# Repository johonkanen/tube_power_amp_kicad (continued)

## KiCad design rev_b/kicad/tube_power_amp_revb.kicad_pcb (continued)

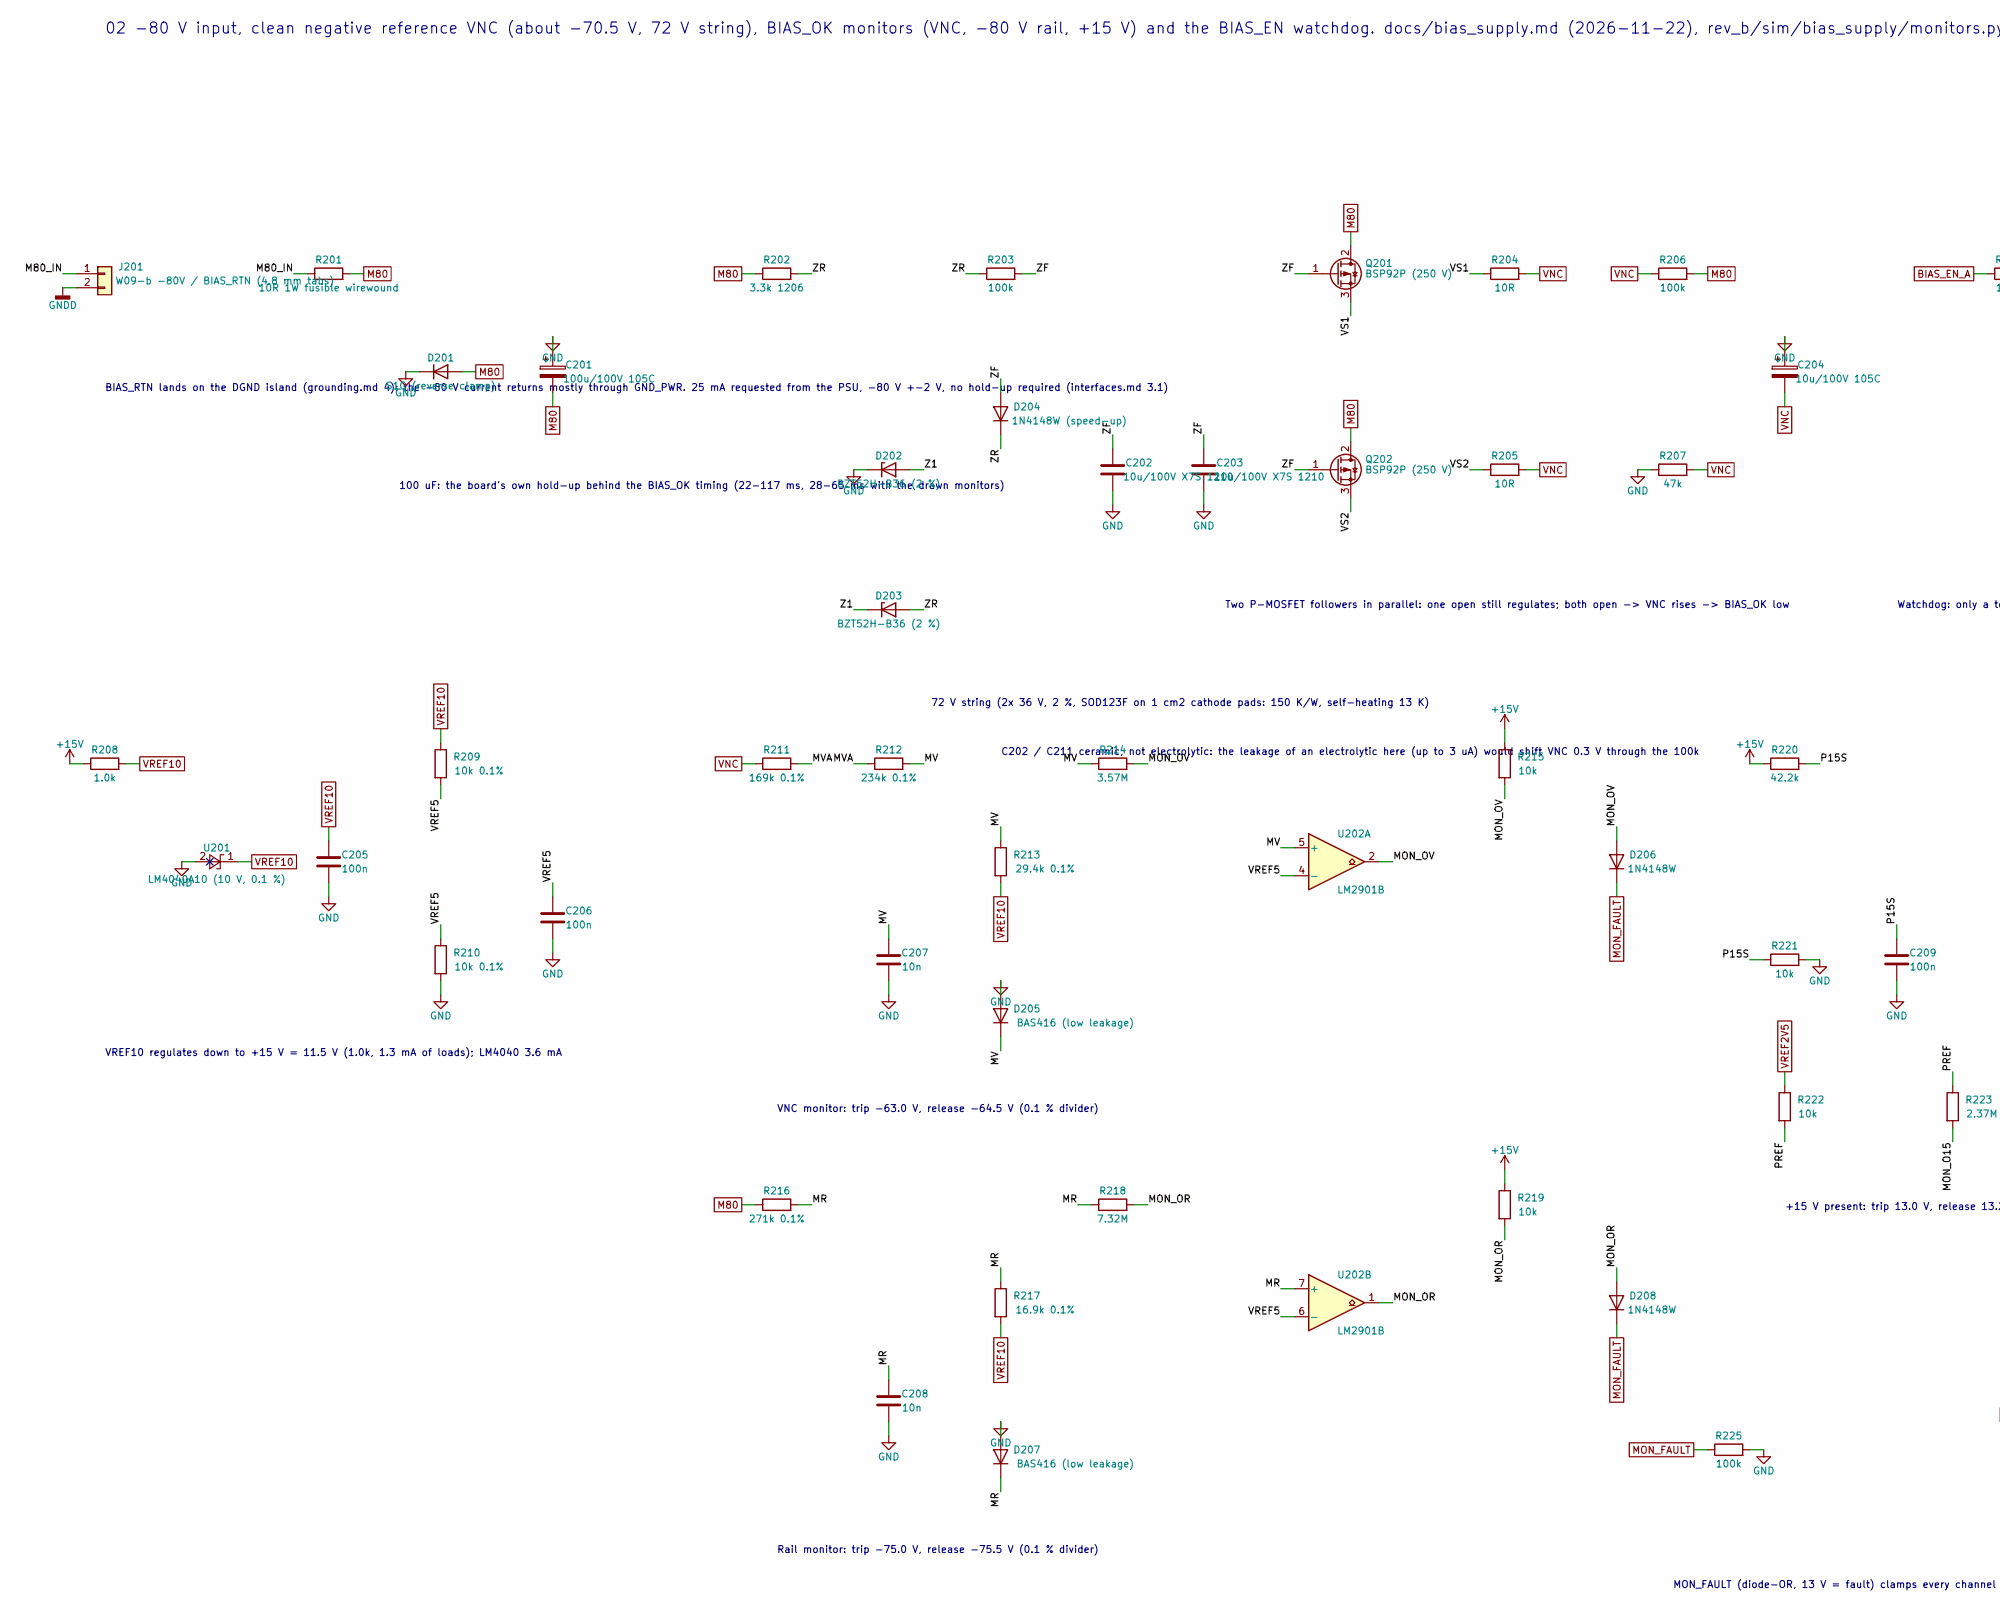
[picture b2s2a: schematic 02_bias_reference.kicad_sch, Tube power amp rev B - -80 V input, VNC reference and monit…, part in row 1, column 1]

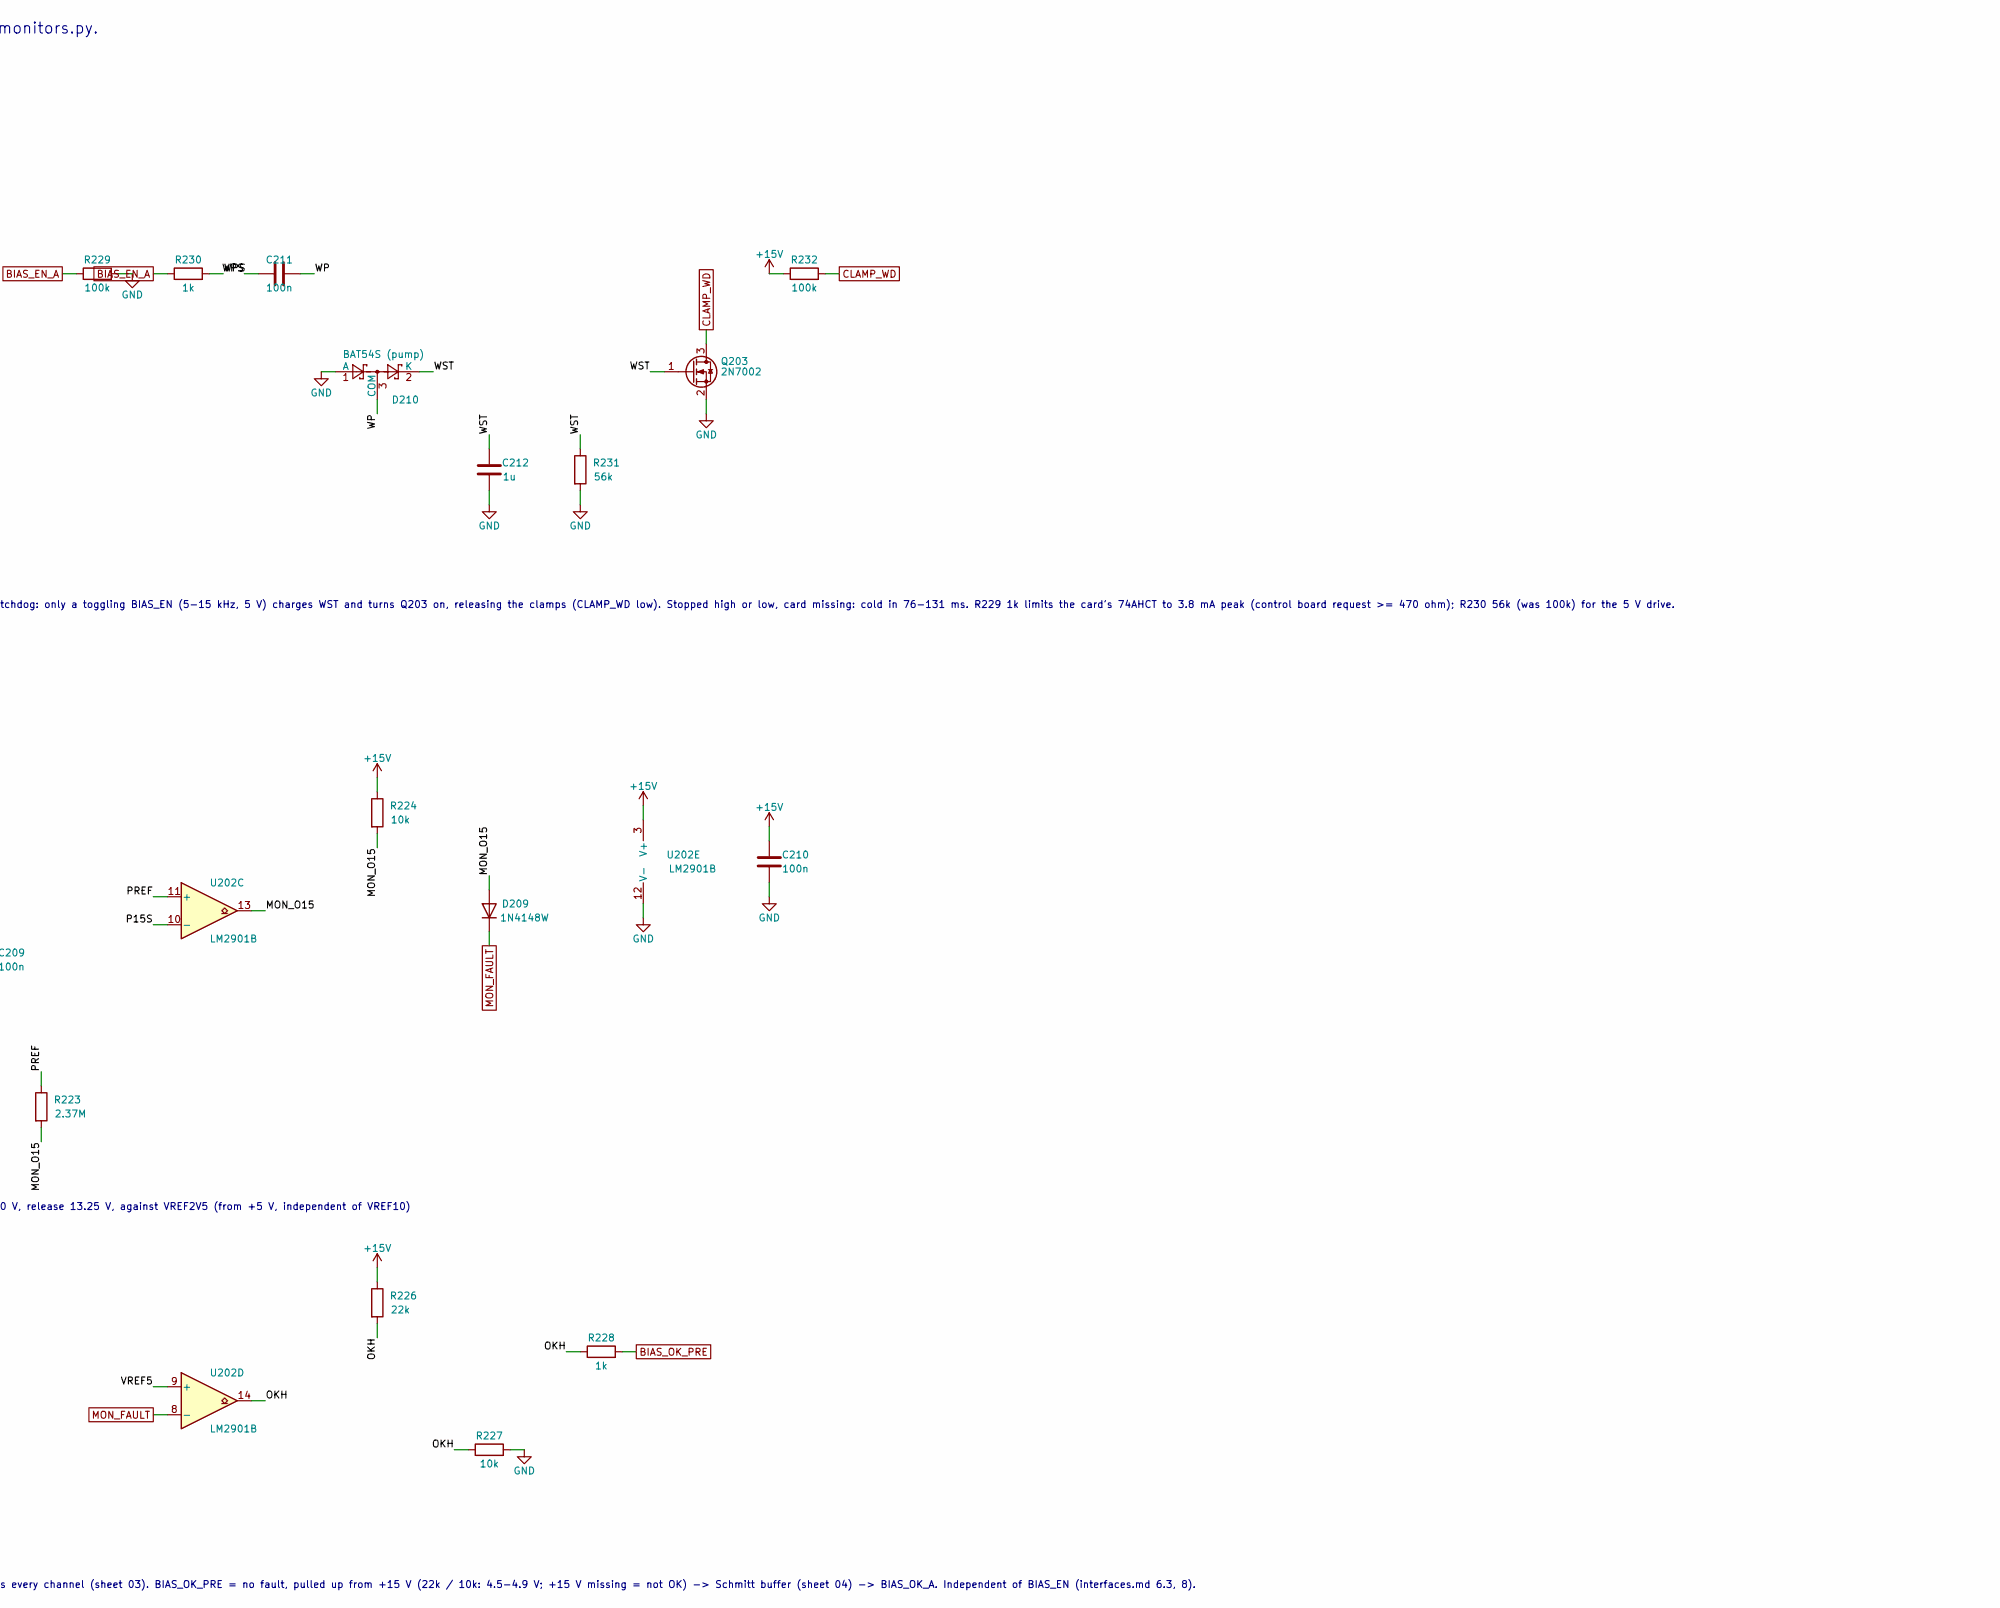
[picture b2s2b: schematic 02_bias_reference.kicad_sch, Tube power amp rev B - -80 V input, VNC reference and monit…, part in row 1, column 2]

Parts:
C201: 100u/100V 105C; CP_Radial_D10.0mm_P5.00mm
C202, C203: 10u/100V X7S 1210; C_1210_3225Metric
C204: 10u/100V 105C; CP_Radial_D6.3mm_P2.50mm
C205, C206, C209, C210, C211: 100n; C_0603_1608Metric
C207, C208: 10n; C_0603_1608Metric
C212: 1u; C_0603_1608Metric
D201: S1G (reverse clamp); D_SMA
D202, D203: BZT52H-B36 (2 %); D_SOD-123F
D204: 1N4148W (speed-up); D_SOD-123
D205, D207: BAS416 (low leakage); D_SOD-323
D206, D208, D209: 1N4148W; D_SOD-123
D210: BAT54S (pump); SOT-23
J201: W09-b -80V / BIAS_RTN (4.8 mm tabs); BladeTab_4.8mm_x2_P9.50mm
Q201, Q202: BSP92P (250 V); SOT-223-3_TabPin2
Q203: 2N7002; SOT-23
R201: 10R 1W fusible wirewound; R_Axial_DIN0309_L9.0mm_D3.2mm_P12.70mm_Horizontal
R202: 3.3k 1206; R_1206_3216Metric
R203, R206, R225, R229, R232: 100k; R_0603_1608Metric
R204, R205: 10R; R_0603_1608Metric
R207: 47k; R_0603_1608Metric
R208: 1.0k; R_1206_3216Metric
R209, R210: 10k 0.1%; R_1206_3216Metric
R211: 169k 0.1%; R_1206_3216Metric
R212: 234k 0.1%; R_1206_3216Metric
R213: 29.4k 0.1%; R_1206_3216Metric
R214: 3.57M; R_1206_3216Metric
R215, R219, R221, R222, R224, R227: 10k; R_0603_1608Metric
R216: 271k 0.1%; R_1206_3216Metric
R217: 16.9k 0.1%; R_1206_3216Metric
R218: 7.32M; R_1206_3216Metric
R220: 42.2k; R_0603_1608Metric
R223: 2.37M; R_1206_3216Metric
R226: 22k; R_0603_1608Metric
R228, R230: 1k; R_0603_1608Metric
R231: 56k; R_0603_1608Metric
U201: LM4040A10 (10 V, 0.1 %); SOT-23
U202: LM2901B; SOIC-14_3.9x8.7mm_P1.27mm

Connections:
+15V: C210.1, R208.1, R215.1, R219.1, R220.1, R224.1, R226.1, R232.1, U202.3 (V+); also elsewhere on the board
/02 -80 V input, VNC reference and monitor, watchdog/M80_IN: J201.1, R201.1
/02 -80 V input, VNC reference and monitor, watchdog/MON_O15: D209.2 (A), R223.2, R224.2, U202.13
/02 -80 V input, VNC reference and monitor, watchdog/MON_OR: D208.2 (A), R218.2, R219.2, U202.1
/02 -80 V input, VNC reference and monitor, watchdog/MON_OV: D206.2 (A), R214.2, R215.2, U202.2
/02 -80 V input, VNC reference and monitor, watchdog/MR: C208.1, D207.1 (K), R216.2, R217.1, R218.1, U202.7 (+)
/02 -80 V input, VNC reference and monitor, watchdog/MV: C207.1, D205.1 (K), R212.2, R213.1, R214.1, U202.5 (+)
/02 -80 V input, VNC reference and monitor, watchdog/MVA: R211.2, R212.1
/02 -80 V input, VNC reference and monitor, watchdog/OKH: R226.2, R227.1, R228.1, U202.14
/02 -80 V input, VNC reference and monitor, watchdog/P15S: C209.1, R220.2, R221.1, U202.10 (-)
/02 -80 V input, VNC reference and monitor, watchdog/PREF: R222.2, R223.1, U202.11 (+)
/02 -80 V input, VNC reference and monitor, watchdog/VREF5: C206.1, R209.2, R210.1, U202.4 (-), U202.6 (-), U202.9 (+)
/02 -80 V input, VNC reference and monitor, watchdog/VS1: Q201.3 (S), R204.1
/02 -80 V input, VNC reference and monitor, watchdog/VS2: Q202.3 (S), R205.1
/02 -80 V input, VNC reference and monitor, watchdog/WP: C211.2, D210.3 (COM)
/02 -80 V input, VNC reference and monitor, watchdog/WPS: C211.1, R230.2
/02 -80 V input, VNC reference and monitor, watchdog/WST: C212.1, D210.2 (K), Q203.1 (G), R231.1
/02 -80 V input, VNC reference and monitor, watchdog/Z1: D202.2 (A), D203.1 (K)
/02 -80 V input, VNC reference and monitor, watchdog/ZF: C202.1, C203.1, D204.2 (A), Q201.1 (G), Q202.1 (G), R203.2
/02 -80 V input, VNC reference and monitor, watchdog/ZR: D203.2 (A), D204.1 (K), R202.2, R203.1
BIAS_EN_A: R229.1, R230.1; also elsewhere on the board
BIAS_OK_PRE: R228.2; also elsewhere on the board
CLAMP_WD: Q203.3 (D), R232.2; also elsewhere on the board
GND: C201.1, C202.2, C203.2, C204.1, C205.2, C206.2, C207.2, C208.2, C209.2, C210.2, C212.2, D201.1 (K), D202.1 (K), D205.2 (A), D207.2 (A), D210.1 (A), Q203.2 (S), R207.1, R210.2, R221.2, R225.2, R227.2, R229.2, R231.2, U201.2 (A), U202.12 (V-); also elsewhere on the board
GNDD: J201.2; also elsewhere on the board
M80: C201.2, D201.2 (A), Q201.2 (D), Q202.2 (D), R201.2, R202.1, R206.2, R216.1; also elsewhere on the board
MON_FAULT: D206.1 (K), D208.1 (K), D209.1 (K), R225.1, U202.8 (-); also elsewhere on the board
VNC: C204.2, R204.2, R205.2, R206.1, R207.2, R211.1; also elsewhere on the board
VREF2V5: R222.1; also elsewhere on the board
VREF10: C205.1, R208.2, R209.1, R213.2, R217.2, U201.1 (K); also elsewhere on the board

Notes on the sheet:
02 -80 V input, clean negative reference VNC (about -70.5 V, 72 V string), BIAS_OK monitors (VNC, -80 V rail, +15 V) and the BIAS_EN watchdog. docs/bias_supply.md (2026-11-22), rev_b/sim/bias_supply/monitors.py.
BIAS_RTN lands on the DGND island (grounding.md 4); the -80 V current returns mostly through GND_PWR. 25 mA requested from the PSU, -80 V +-2 V, no hold-up required (interfaces.md 3.1)
100 uF: the board's own hold-up behind the BIAS_OK timing (22-117 ms, 28-65 ms with the drawn monitors)
72 V string (2x 36 V, 2 %, SOD123F on 1 cm2 cathode pads: 150 K/W, self-heating 13 K)
C202 / C211 ceramic, not electrolytic: the leakage of an electrolytic here (up to 3 uA) would shift VNC 0.3 V through the 100k
Two P-MOSFET followers in parallel: one open still regulates; both open -> VNC rises -> BIAS_OK low
VREF10 regulates down to +15 V = 11.5 V (1.0k, 1.3 mA of loads); LM4040 3.6 mA
VNC monitor: trip -63.0 V, release -64.5 V (0.1 % divider)
Rail monitor: trip -75.0 V, release -75.5 V (0.1 % divider)
+15 V present: trip 13.0 V, release 13.25 V, against VREF2V5 (from +5 V, independent of VREF10)
MON_FAULT (diode-OR, 13 V = fault) clamps every channel (sheet 03). BIAS_OK_PRE = no fault, pulled up from +15 V (22k / 10k: 4.5-4.9 V; +15 V missing = not OK) -> Schmitt buffer (sheet 04) -> BIAS_OK_A. Independent of BIAS_EN (interfaces.md 6.3, 8).
Watchdog: only a toggling BIAS_EN (5-15 kHz, 5 V) charges WST and turns Q203 on, releasing the clamps (CLAMP_WD low). Stopped high or low, card missing: cold in 76-131 ms. R229 1k limits the card's 74AHCT to 3.8 mA peak (control board request >= 470 ohm); R230 56k (was 100k) for the 5 V drive.

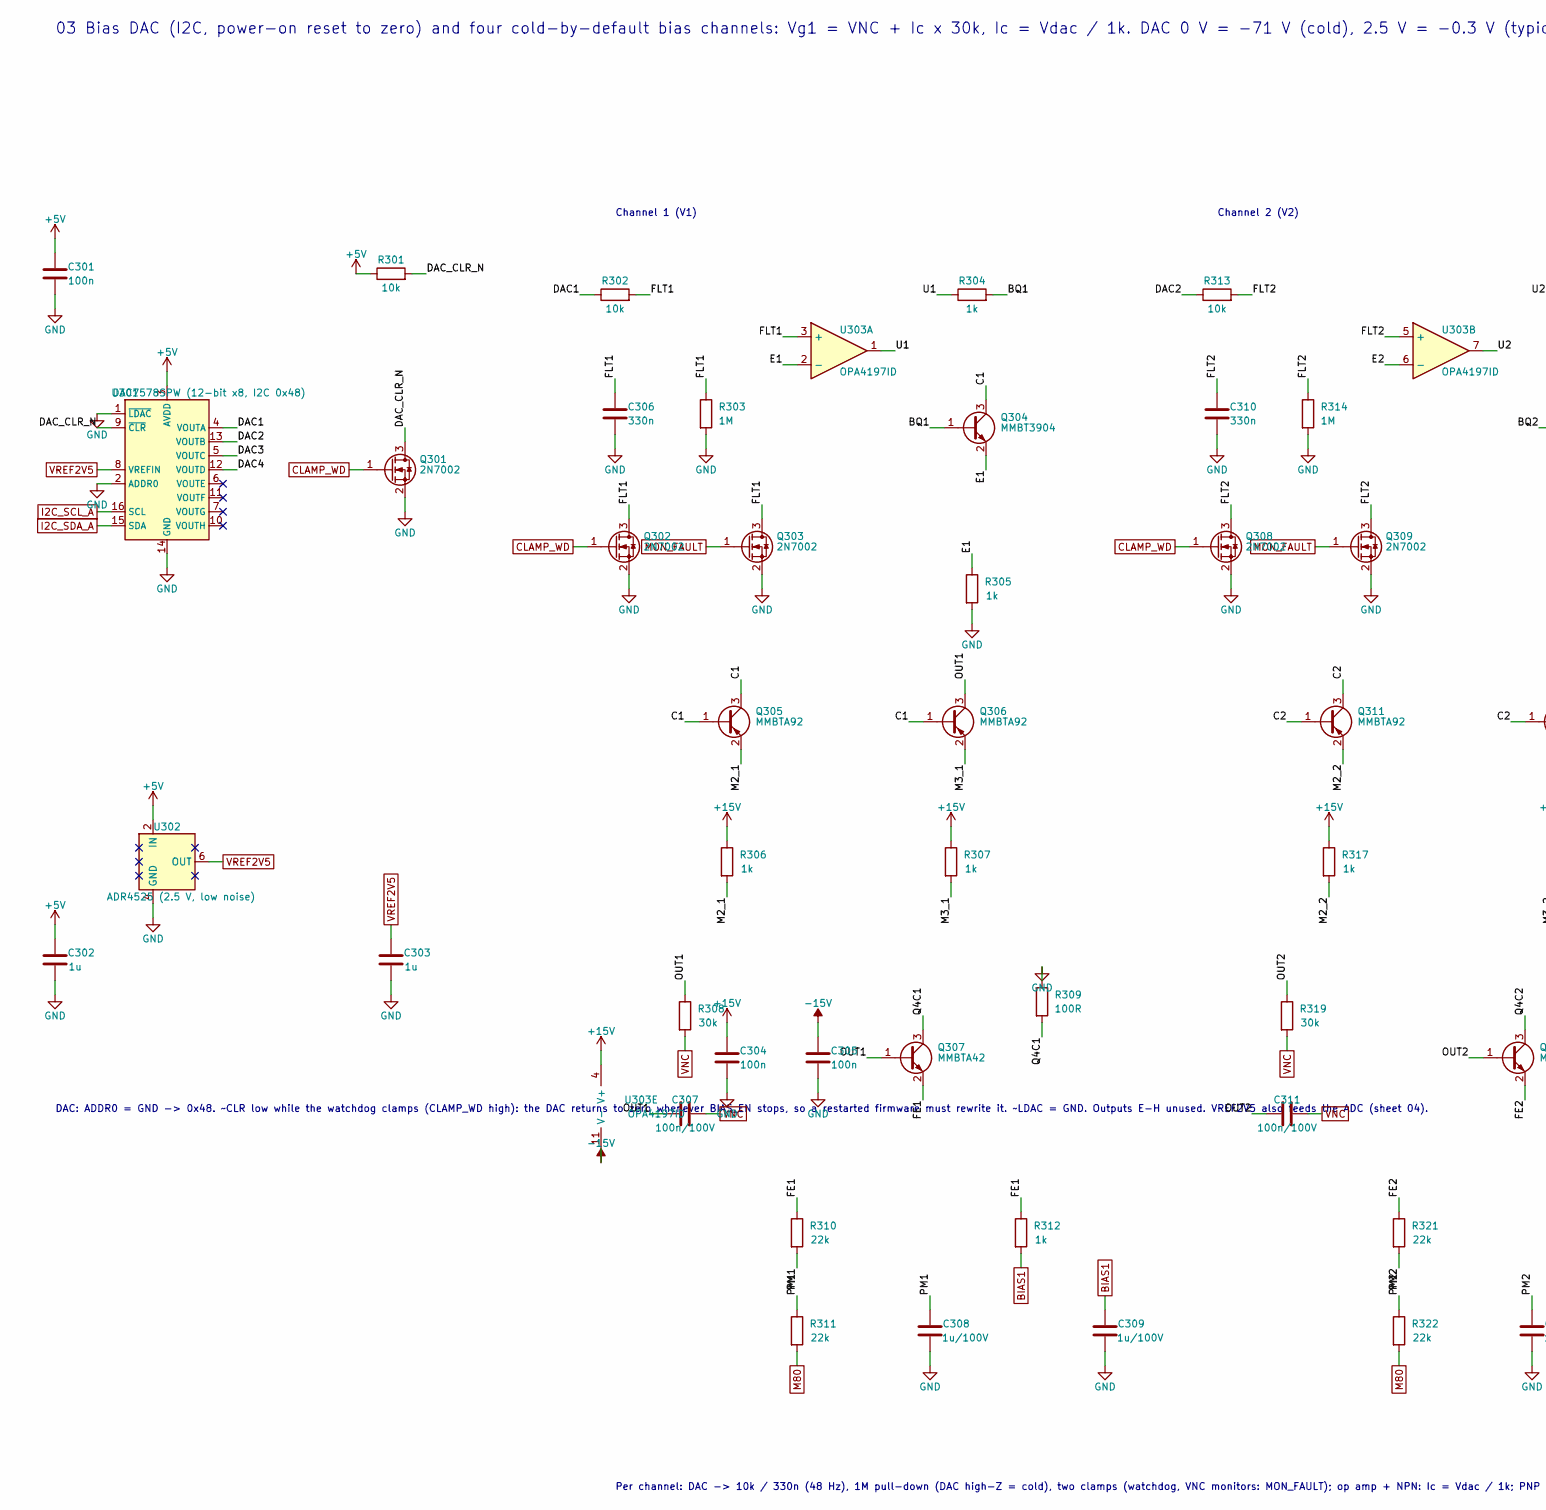
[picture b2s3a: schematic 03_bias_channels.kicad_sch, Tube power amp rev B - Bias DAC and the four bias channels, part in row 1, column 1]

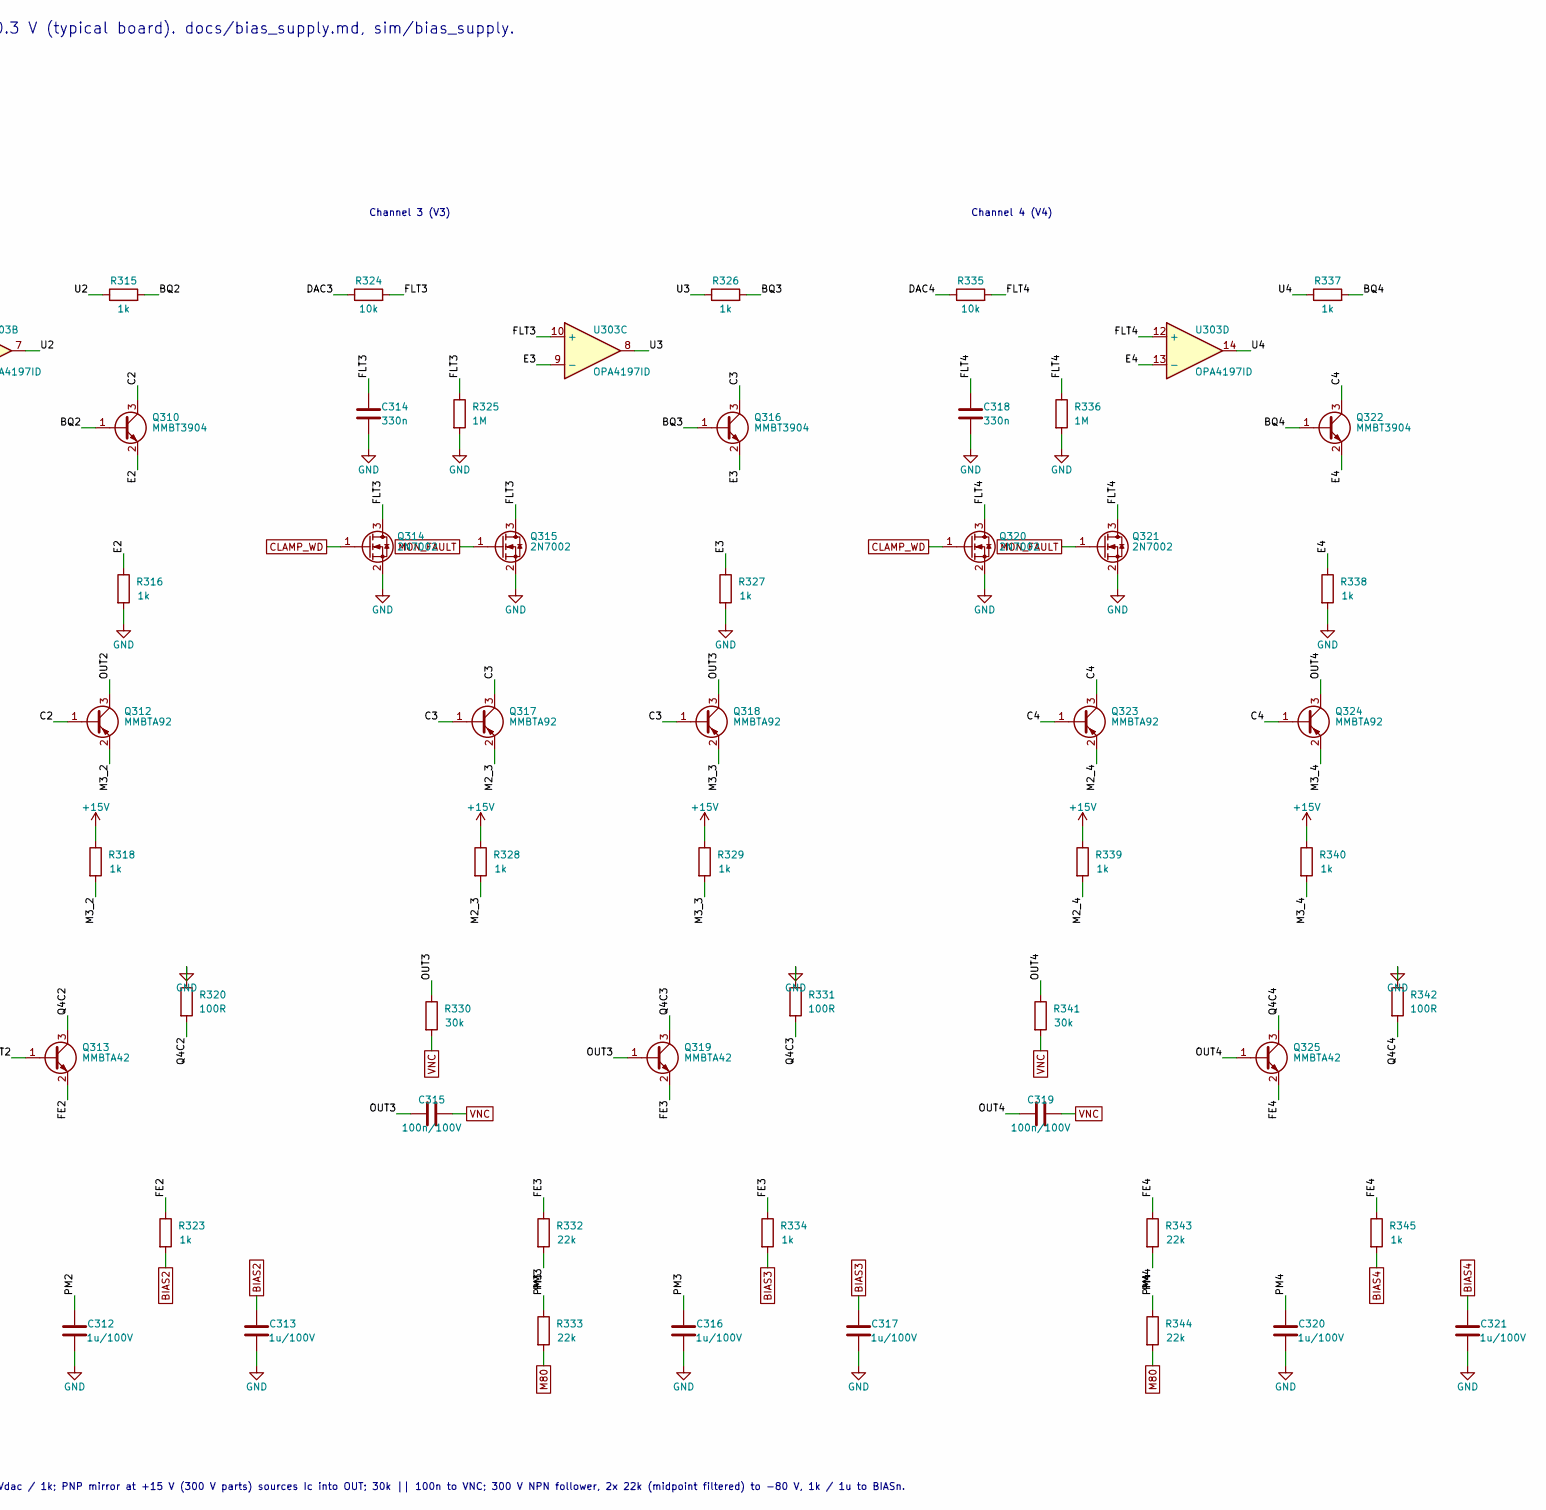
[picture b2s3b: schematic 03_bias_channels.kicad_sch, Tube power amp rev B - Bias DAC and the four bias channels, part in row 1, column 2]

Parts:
C301, C304, C305: 100n; C_0603_1608Metric
C302, C303: 1u; C_0603_1608Metric
C306, C310, C314, C318: 330n; C_0805_2012Metric
C307, C311, C315, C319: 100n/100V; C_0805_2012Metric
C308, C309, C312, C313, C316, C317, C320, C321: 1u/100V; C_0805_2012Metric
Q301, Q302, Q303, Q308, Q309, Q314, Q315, Q320, Q321: 2N7002; SOT-23
Q304, Q310, Q316, Q322: MMBT3904; SOT-23
Q305, Q306, Q311, Q312, Q317, Q318, Q323, Q324: MMBTA92; SOT-23
Q307, Q313, Q319, Q325: MMBTA42; SOT-23
R301, R302, R313, R324, R335: 10k; R_0603_1608Metric
R303, R314, R325, R336: 1M; R_1206_3216Metric
R304, R305, R306, R307, R312, R315, R316, R317, R318, R323, R326, R327, R328, R329, R334, R337, R338, R339, R340, R345: 1k; R_0603_1608Metric
R308, R319, R330, R341: 30k; R_0603_1608Metric
R309, R320, R331, R342: 100R; R_0603_1608Metric
R310, R311, R321, R322, R332, R333, R343, R344: 22k; R_0603_1608Metric
U301: DAC7578SPW (12-bit x8, I2C 0x48); TSSOP-16_4.4x5mm_P0.65mm
U302: ADR4525 (2.5 V, low noise); SOIC-8_3.9x4.9mm_P1.27mm
U303: OPA4197ID; SOIC-14_3.9x8.7mm_P1.27mm

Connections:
+5V: C301.1, C302.1, R301.1, U301.3 (AVDD), U302.2 (IN); also elsewhere on the board
+15V: C304.1, R306.1, R307.1, R317.1, R318.1, R328.1, R329.1, R339.1, R340.1, U303.4 (V+); also elsewhere on the board
-15V: C305.1, U303.11 (V-); also elsewhere on the board
/03 Bias DAC and the four bias channels/BQ1: Q304.1 (B), R304.2
/03 Bias DAC and the four bias channels/BQ2: Q310.1 (B), R315.2
/03 Bias DAC and the four bias channels/BQ3: Q316.1 (B), R326.2
/03 Bias DAC and the four bias channels/BQ4: Q322.1 (B), R337.2
/03 Bias DAC and the four bias channels/C1: Q304.3 (C), Q305.1 (B), Q305.3 (C), Q306.1 (B)
/03 Bias DAC and the four bias channels/C2: Q310.3 (C), Q311.1 (B), Q311.3 (C), Q312.1 (B)
/03 Bias DAC and the four bias channels/C3: Q316.3 (C), Q317.1 (B), Q317.3 (C), Q318.1 (B)
/03 Bias DAC and the four bias channels/C4: Q322.3 (C), Q323.1 (B), Q323.3 (C), Q324.1 (B)
/03 Bias DAC and the four bias channels/DAC1: R302.1, U301.4 (VOUTA)
/03 Bias DAC and the four bias channels/DAC2: R313.1, U301.13 (VOUTB)
/03 Bias DAC and the four bias channels/DAC3: R324.1, U301.5 (VOUTC)
/03 Bias DAC and the four bias channels/DAC4: R335.1, U301.12 (VOUTD)
/03 Bias DAC and the four bias channels/DAC_CLR_N: Q301.3 (D), R301.2, U301.9 (~CLR)
/03 Bias DAC and the four bias channels/E1: Q304.2 (E), R305.1, U303.2 (-)
/03 Bias DAC and the four bias channels/E2: Q310.2 (E), R316.1, U303.6 (-)
/03 Bias DAC and the four bias channels/E3: Q316.2 (E), R327.1, U303.9 (-)
/03 Bias DAC and the four bias channels/E4: Q322.2 (E), R338.1, U303.13 (-)
/03 Bias DAC and the four bias channels/FE1: Q307.2 (E), R310.1, R312.1
/03 Bias DAC and the four bias channels/FE2: Q313.2 (E), R321.1, R323.1
/03 Bias DAC and the four bias channels/FE3: Q319.2 (E), R332.1, R334.1
/03 Bias DAC and the four bias channels/FE4: Q325.2 (E), R343.1, R345.1
/03 Bias DAC and the four bias channels/FLT1: C306.1, Q302.3 (D), Q303.3 (D), R302.2, R303.1, U303.3 (+)
/03 Bias DAC and the four bias channels/FLT2: C310.1, Q308.3 (D), Q309.3 (D), R313.2, R314.1, U303.5 (+)
/03 Bias DAC and the four bias channels/FLT3: C314.1, Q314.3 (D), Q315.3 (D), R324.2, R325.1, U303.10 (+)
/03 Bias DAC and the four bias channels/FLT4: C318.1, Q320.3 (D), Q321.3 (D), R335.2, R336.1, U303.12 (+)
/03 Bias DAC and the four bias channels/M2_1: Q305.2 (E), R306.2
/03 Bias DAC and the four bias channels/M2_2: Q311.2 (E), R317.2
/03 Bias DAC and the four bias channels/M2_3: Q317.2 (E), R328.2
/03 Bias DAC and the four bias channels/M2_4: Q323.2 (E), R339.2
/03 Bias DAC and the four bias channels/M3_1: Q306.2 (E), R307.2
/03 Bias DAC and the four bias channels/M3_2: Q312.2 (E), R318.2
/03 Bias DAC and the four bias channels/M3_3: Q318.2 (E), R329.2
/03 Bias DAC and the four bias channels/M3_4: Q324.2 (E), R340.2
/03 Bias DAC and the four bias channels/OUT1: C307.1, Q306.3 (C), Q307.1 (B), R308.1
/03 Bias DAC and the four bias channels/OUT2: C311.1, Q312.3 (C), Q313.1 (B), R319.1
/03 Bias DAC and the four bias channels/OUT3: C315.1, Q318.3 (C), Q319.1 (B), R330.1
/03 Bias DAC and the four bias channels/OUT4: C319.1, Q324.3 (C), Q325.1 (B), R341.1
/03 Bias DAC and the four bias channels/PM1: C308.1, R310.2, R311.1
/03 Bias DAC and the four bias channels/PM2: C312.1, R321.2, R322.1
/03 Bias DAC and the four bias channels/PM3: C316.1, R332.2, R333.1
/03 Bias DAC and the four bias channels/PM4: C320.1, R343.2, R344.1
/03 Bias DAC and the four bias channels/Q4C1: Q307.3 (C), R309.2
/03 Bias DAC and the four bias channels/Q4C2: Q313.3 (C), R320.2
/03 Bias DAC and the four bias channels/Q4C3: Q319.3 (C), R331.2
/03 Bias DAC and the four bias channels/Q4C4: Q325.3 (C), R342.2
/03 Bias DAC and the four bias channels/U1: R304.1, U303.1
/03 Bias DAC and the four bias channels/U2: R315.1, U303.7
/03 Bias DAC and the four bias channels/U3: R326.1, U303.8
/03 Bias DAC and the four bias channels/U4: R337.1, U303.14
BIAS1: C309.1, R312.2; also elsewhere on the board
BIAS2: C313.1, R323.2; also elsewhere on the board
BIAS3: C317.1, R334.2; also elsewhere on the board
BIAS4: C321.1, R345.2; also elsewhere on the board
CLAMP_WD: Q301.1 (G), Q302.1 (G), Q308.1 (G), Q314.1 (G), Q320.1 (G); also elsewhere on the board
GND: C301.2, C302.2, C303.2, C304.2, C305.2, C306.2, C308.2, C309.2, C310.2, C312.2, C313.2, C314.2, C316.2, C317.2, C318.2, C320.2, C321.2, Q301.2 (S), Q302.2 (S), Q303.2 (S), Q308.2 (S), Q309.2 (S), Q314.2 (S), Q315.2 (S), Q320.2 (S), Q321.2 (S), R303.2, R305.2, R309.1, R314.2, R316.2, R320.1, R325.2, R327.2, R331.1, R336.2, R338.2, R342.1, U301.1 (~LDAC), U301.2 (ADDR0), U301.14 (GND), U302.4 (GND); also elsewhere on the board
I2C_SCL_A: U301.16 (SCL); also elsewhere on the board
I2C_SDA_A: U301.15 (SDA); also elsewhere on the board
M80: R311.2, R322.2, R333.2, R344.2; also elsewhere on the board
MON_FAULT: Q303.1 (G), Q309.1 (G), Q315.1 (G), Q321.1 (G); also elsewhere on the board
VNC: C307.2, C311.2, C315.2, C319.2, R308.2, R319.2, R330.2, R341.2; also elsewhere on the board
VREF2V5: C303.1, U301.8 (VREFIN), U302.6 (OUT); also elsewhere on the board

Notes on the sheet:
03 Bias DAC (I2C, power-on reset to zero) and four cold-by-default bias channels: Vg1 = VNC + Ic x 30k, Ic = Vdac / 1k. DAC 0 V = -71 V (cold), 2.5 V = -0.3 V (typical board). docs/bias_supply.md, sim/bias_supply.
DAC: ADDR0 = GND -> 0x48. ~CLR low while the watchdog clamps (CLAMP_WD high): the DAC returns to zero whenever BIAS_EN stops, so a restarted firmware must rewrite it. ~LDAC = GND. Outputs E-H unused. VREF2V5 also feeds the ADC (sheet 04).
Channel 1 (V1)
Channel 2 (V2)
Channel 3 (V3)
Channel 4 (V4)
Per channel: DAC -> 10k / 330n (48 Hz), 1M pull-down (DAC high-Z = cold), two clamps (watchdog, VNC monitors: MON_FAULT); op amp + NPN: Ic = Vdac / 1k; PNP mirror at +15 V (300 V parts) sources Ic into OUT; 30k || 100n to VNC; 300 V NPN follower, 2x 22k (midpoint filtered) to -80 V, 1k / 1u to BIAS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
